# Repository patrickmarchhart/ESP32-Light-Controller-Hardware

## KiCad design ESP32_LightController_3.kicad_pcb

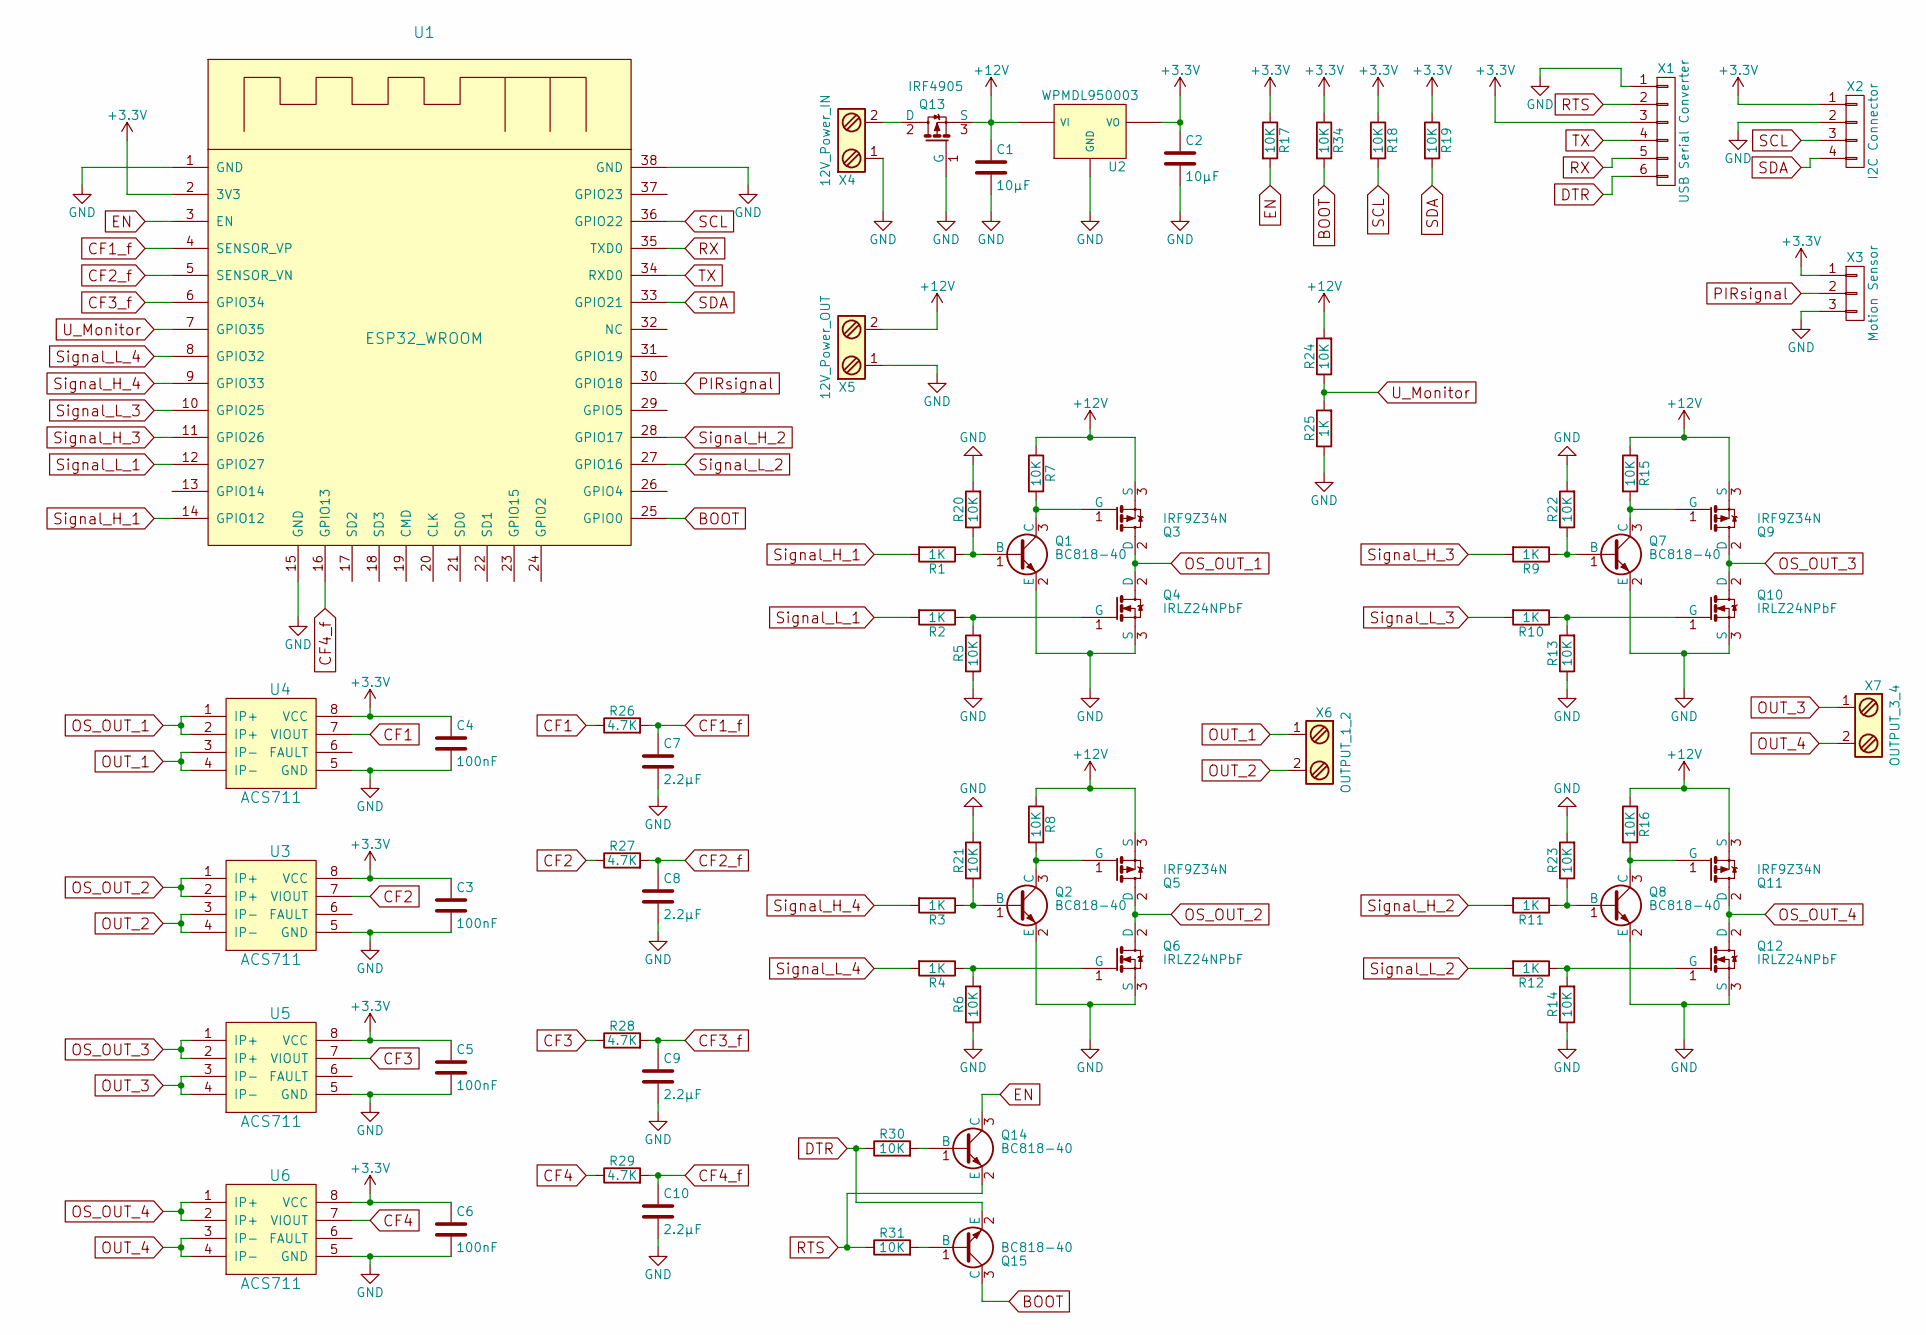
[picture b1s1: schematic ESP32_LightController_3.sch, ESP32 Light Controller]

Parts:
C1, C2: 10µF; C_0805_HandSoldering
C3, C4, C5, C6: 100nF; C_0805_HandSoldering
C7, C8, C9, C10: 2.2µF; C_0805_HandSoldering
Q1, Q2, Q7, Q8, Q14, Q15: BC818-40; SOT-23
Q3, Q5, Q9, Q11: IRF9Z34N; TO-220_Vertical
Q4, Q6, Q10, Q12: IRLZ24NPbF; TO-220_Vertical
Q13: IRF4905; TO-220_Vertical
R1, R2, R3, R4, R9, R10, R11, R12, R25: 1K; R_0805_HandSoldering
R5, R6, R7, R8, R13, R14, R15, R16, R17, R18, R19, R20, R21, R22, R23, R24, R30, R31, R34: 10K; R_0805_HandSoldering
R26, R27, R28, R29: 4.7K; R_0805_HandSoldering
U1: ESP32_WROOM
U2: WPMDL950003; DCDC-Conv_TRACO_TSR-1
U3, U4, U5, U6: ACS711; SOIC-8_3.9x4.9mm_Pitch1.27mm
X1: USB Serial Converter; Socket_Strip_Straight_1x06_Pitch2.54mm
X2: I2C Connector; Socket_Strip_Straight_1x04_Pitch2.54mm
X3: Motion Sensor; Socket_Strip_Straight_1x03_Pitch2.54mm
X4: 12V_Power_IN; TerminalBlock_PTR_AKZ500-2DS-5.08-V
X5: 12V_Power_OUT; TerminalBlock_PTR_AKZ500-2DS-5.08-V
X6: OUTPUT_1_2; TerminalBlock_PTR_AKZ500-2DS-5.08-V
X7: OUTPUT_3_4; TerminalBlock_PTR_AKZ500-2DS-5.08-V

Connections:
+3V3: C2.1, C3.1, C4.1, C5.1, C6.1, R17.1, R18.1, R19.1, R34.1, U1.2 (3V3), U2.3 (VO), U3.8 (VCC), U4.8 (VCC), U5.8 (VCC), U6.8 (VCC), X1.3, X2.1, X3.1
+12V: C1.1, Q3.3 (S), Q5.3 (S), Q9.3 (S), Q11.3 (S), Q13.3 (S), R7.1, R8.1, R15.1, R16.1, R24.2, U2.1 (VI), X5.2
BOOT: Q15.3 (C), R34.2, U1.25 (GPIO0)
CF1: R26.1, U4.7 (VIOUT)
CF1_f: C7.1, R26.2, U1.4 (SENSOR_VP)
CF2: R27.1, U3.7 (VIOUT)
CF2_f: C8.1, R27.2, U1.5 (SENSOR_VN)
CF3: R28.1, U5.7 (VIOUT)
CF3_f: C9.1, R28.2, U1.6 (GPIO34)
CF4: R29.1, U6.7 (VIOUT)
CF4_f: C10.1, R29.2, U1.16 (GPIO13)
DTR: Q15.2 (E), R30.1, X1.6
EN: Q14.3 (C), R17.2, U1.3 (EN)
GND: C1.2, C2.2, C3.2, C4.2, C5.2, C6.2, C7.2, C8.2, C9.2, C10.2, Q1.2 (E), Q2.2 (E), Q4.3 (S), Q6.3 (S), Q7.2 (E), Q8.2 (E), Q10.3 (S), Q12.3 (S), Q13.1 (G), R5.1, R6.1, R13.1, R14.1, R20.2, R21.2, R22.2, R23.2, R25.1, U1.1 (GND), U1.15 (GND), U1.38 (GND), U2.2 (GND), U3.5 (GND), U4.5 (GND), U5.5 (GND), U6.5 (GND), X1.1, X2.2, X3.3, X4.1, X5.1
unnamed: Q1.1 (B), R1.1, R20.1
unnamed: Q1.3 (C), Q3.1 (G), R7.2
unnamed: Q2.1 (B), R3.1, R21.1
unnamed: Q2.3 (C), Q5.1 (G), R8.2
unnamed: Q4.1 (G), R2.1, R5.2
unnamed: Q6.1 (G), R4.1, R6.2
unnamed: Q7.1 (B), R9.1, R22.1
unnamed: Q7.3 (C), Q9.1 (G), R15.2
unnamed: Q8.1 (B), R11.1, R23.1
unnamed: Q10.1 (G), R10.1, R13.2
unnamed: Q8.3 (C), Q11.1 (G), R16.2
unnamed: Q12.1 (G), R12.1, R14.2
unnamed: Q13.2 (D), X4.2
unnamed: Q14.1 (B), R30.2
unnamed: Q15.1 (B), R31.2
OS_OUT_1: Q3.2 (D), Q4.2 (D), U4.1 (IP+), U4.2 (IP+)
OS_OUT_2: Q5.2 (D), Q6.2 (D), U3.1 (IP+), U3.2 (IP+)
OS_OUT_3: Q9.2 (D), Q10.2 (D), U5.1 (IP+), U5.2 (IP+)
OS_OUT_4: Q11.2 (D), Q12.2 (D), U6.1 (IP+), U6.2 (IP+)
OUT_1: U4.3 (IP-), U4.4 (IP-), X6.1
OUT_2: U3.3 (IP-), U3.4 (IP-), X6.2
OUT_3: U5.3 (IP-), U5.4 (IP-), X7.1
OUT_4: U6.3 (IP-), U6.4 (IP-), X7.2
PIRsignal: U1.30 (GPIO18), X3.2
RTS: Q14.2 (E), R31.1, X1.2
RX: U1.35 (TXD0), X1.5
SCL: R18.2, U1.36 (GPIO22), X2.3
SDA: R19.2, U1.33 (GPIO21), X2.4
Signal_H_1: R1.2, U1.14 (GPIO12)
Signal_H_2: R11.2, U1.28 (GPIO17)
Signal_H_3: R9.2, U1.11 (GPIO26)
Signal_H_4: R3.2, U1.9 (GPIO33)
Signal_L_1: R2.2, U1.12 (GPIO27)
Signal_L_2: R12.2, U1.27 (GPIO16)
Signal_L_3: R10.2, U1.10 (GPIO25)
Signal_L_4: R4.2, U1.8 (GPIO32)
TX: U1.34 (RXD0), X1.4
U_Monitor: R24.1, R25.2, U1.7 (GPIO35)

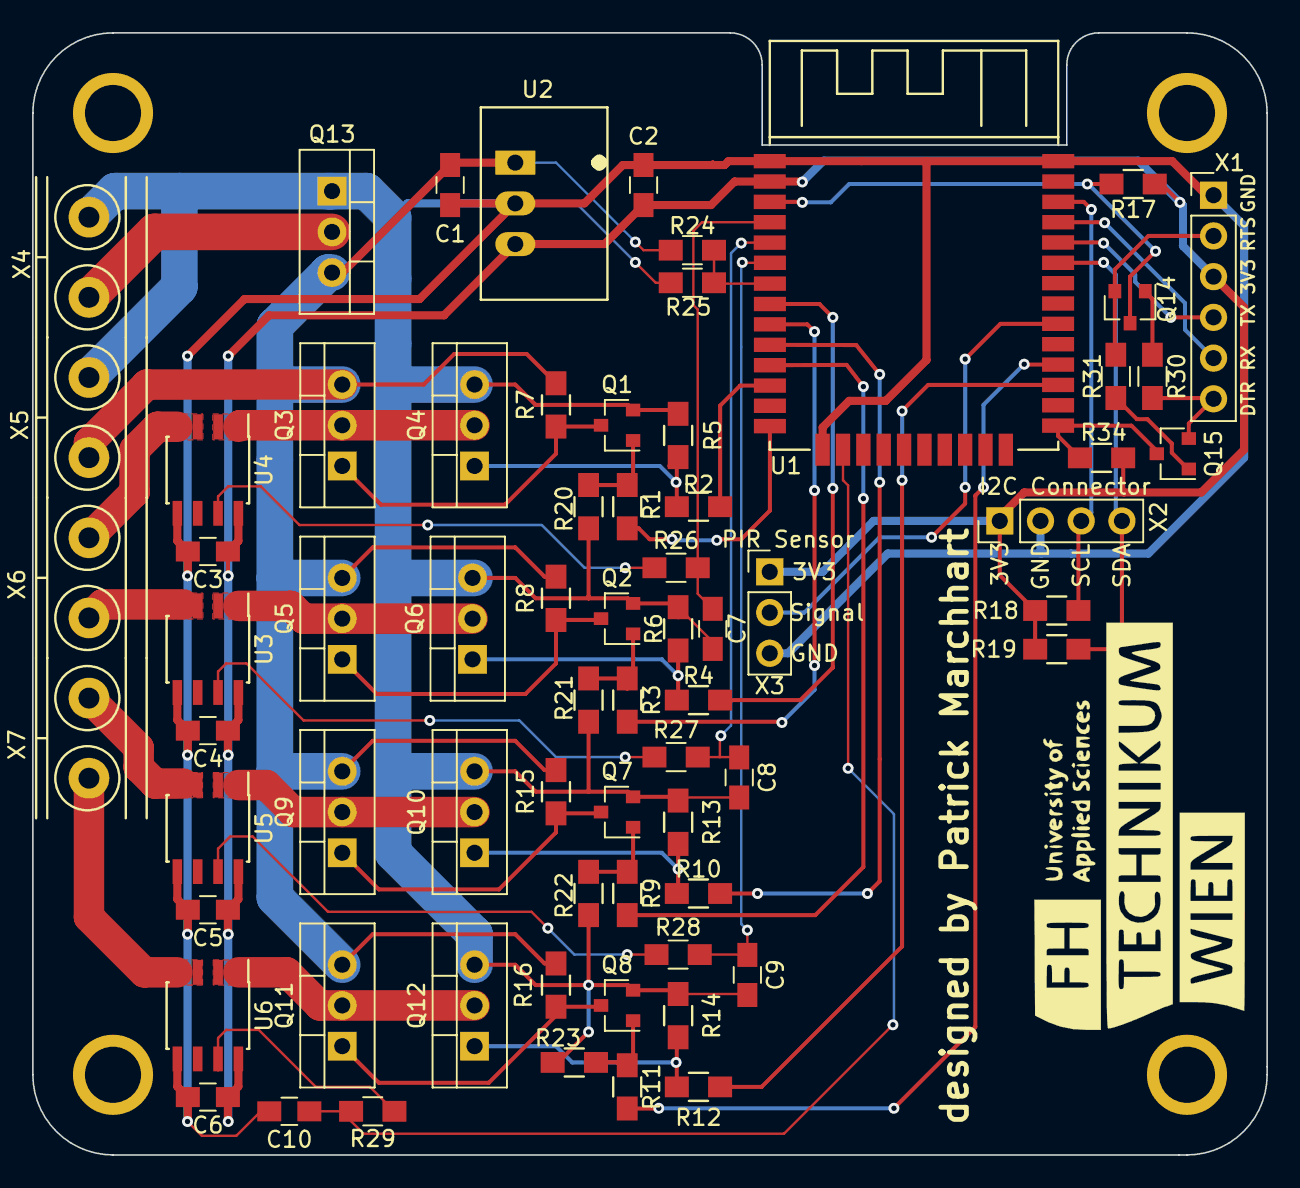
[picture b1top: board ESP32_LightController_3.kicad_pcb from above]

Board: 2 copper layers, 77.0 x 70.0 mm, 70 parts (0 on the bottom side), 52 nets.

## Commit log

2017-04-05 Release
    Release of Revision 3
